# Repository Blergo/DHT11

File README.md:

**Slave with a single DHT22 sensor for the Vivarium Controller project - For more information please see "VivariumController---Master" Repository.**

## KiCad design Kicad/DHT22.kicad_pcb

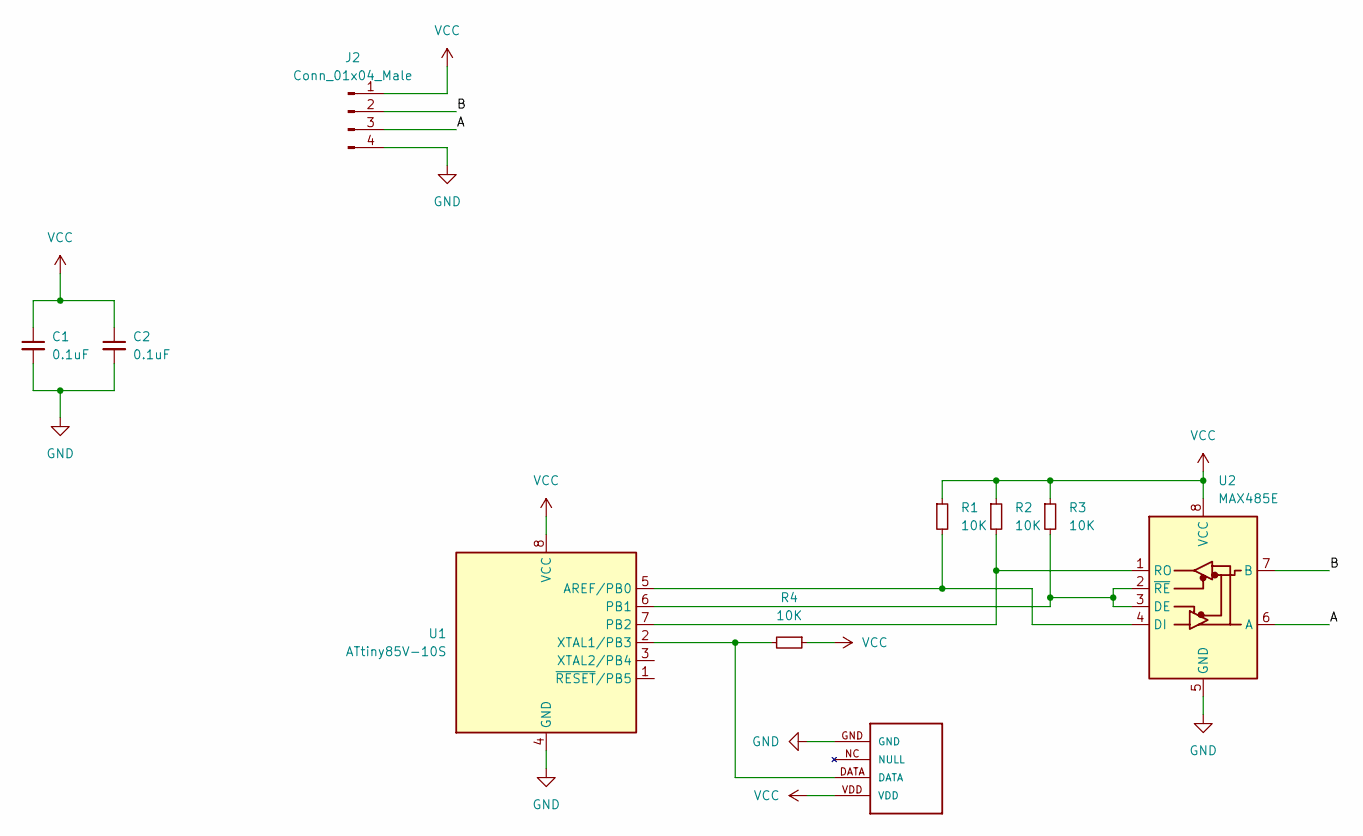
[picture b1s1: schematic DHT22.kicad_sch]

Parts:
C1, C2: 0.1uF; C_0805_2012Metric
J2: Conn_01x04_Male; PinHeader_1x04_P1.27mm_Vertical
R1, R2, R3, R4: 10K; R_0603_1608Metric
U1: ATtiny85V-10S; SOIC-8W_5.3x5.3mm_P1.27mm
U2: MAX485E; SOIC-8_3.9x4.9mm_P1.27mm
U3: DHT22

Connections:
/A: J2.3, U2.6 (A); also elsewhere on the board
/B: J2.2, U2.7 (B); also elsewhere on the board
GND: C1.2, C2.2, J2.4, U1.4 (GND), U2.5 (GND), U3.GND; also elsewhere on the board
unnamed: R1.2, U1.5 (AREF/PB0), U2.4 (DI)
unnamed: R2.2, U1.7 (PB2), U2.1 (RO)
unnamed: R3.2, U1.6 (PB1), U2.2 (~RE), U2.3 (DE)
unnamed: R4.2, U1.2 (XTAL1/PB3), U3.DATA
VCC: C1.1, C2.1, J2.1, R1.1, R2.1, R3.1, R4.1, U1.8 (VCC), U2.8 (VCC), U3.VDD

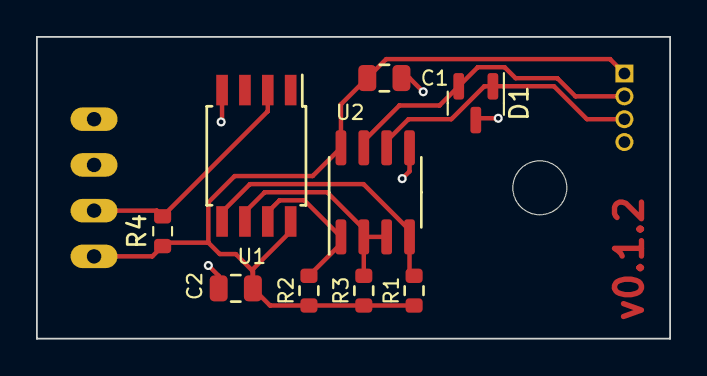
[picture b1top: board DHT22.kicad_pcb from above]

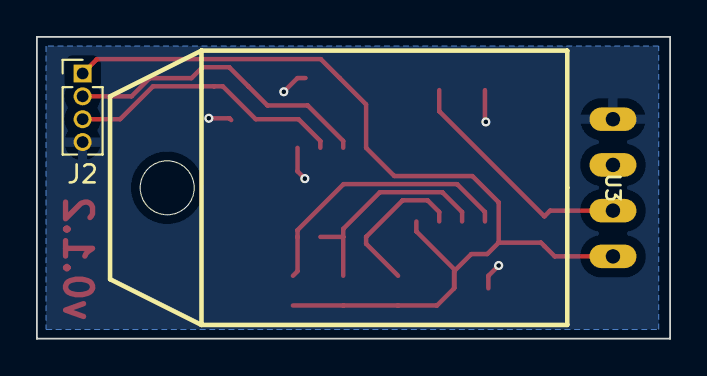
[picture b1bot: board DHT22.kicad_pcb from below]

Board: 2 copper layers, 35.2 x 16.8 mm, 11 parts (2 on the bottom side), 8 nets.

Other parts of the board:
D1: SM712_SOT23; SOT-23

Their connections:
/A: D1.1 (A1); also elsewhere on the board
/B: D1.2 (A2); also elsewhere on the board
GND: D1.3 (common); also elsewhere on the board

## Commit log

2021-12-25 Included libraries
2021-12-25 Initialised SWSerial + DHT
2021-12-25 Changed default slaveID
2021-12-26 changed DHT library
2021-12-26 added some error reporting
2021-12-26 Fixed error register
2021-12-27 Fixed issue with Baud Rate
2021-12-28 Added Ability register
2021-12-28 changes to make modbus respond faster
2021-12-29 Changes to order or registers
2021-12-29 code for controller to set slave ID
2021-12-29 Changed sensor from DHT11 to DHT22
2021-12-29 check slaveid in eeprom isnt 0 before use
2021-12-29 modified modbus library
2021-12-29 Changes to slave ID code
2021-12-30 Removed a delay
2021-12-30 Kicad files for PCB
2021-12-30 Renamed folder for PCB files to Kicad
2022-01-01 Changed slave assignment
2022-01-01 Small change
2022-01-08 Changed Directory name for pcb files
2022-01-09 Updated PCB
